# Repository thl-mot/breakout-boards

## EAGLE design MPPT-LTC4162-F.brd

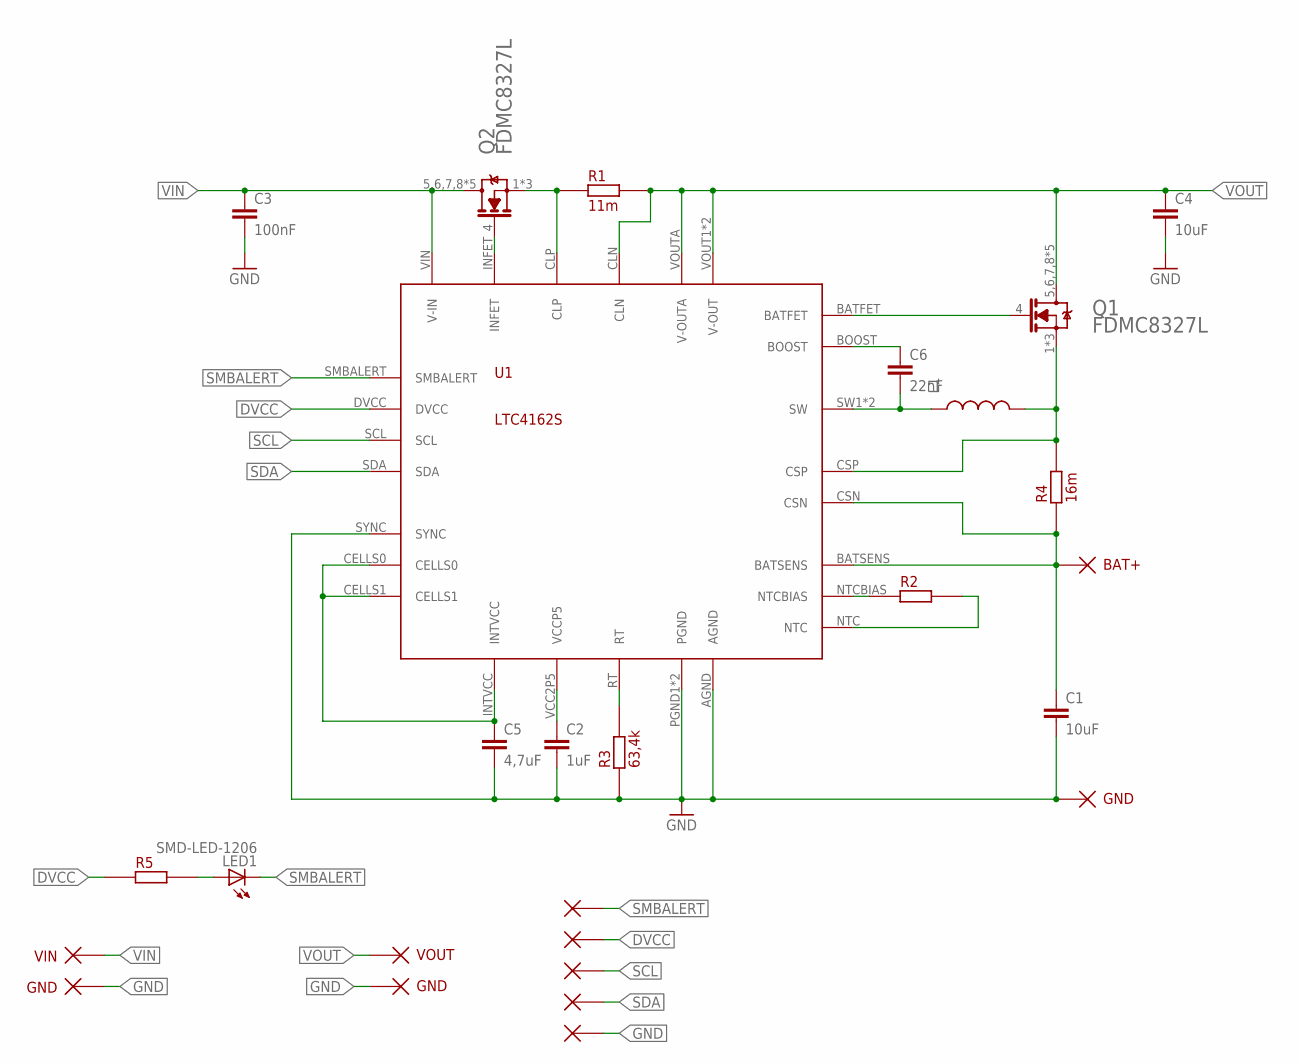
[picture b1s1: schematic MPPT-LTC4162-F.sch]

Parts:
C1, C4: 10uF; C1206
C2: 1uF; C1206
C3: 100nF; C1206
C5: 4,7uF; C1206
C6: 22nF; C1206
L1: L-242408FPS; L-SMD-FPD
LED1: SMD-LED-1206; LED_1206
P1: VIN; PIN
P2, P7, P10: GND; PIN
P3, P4, P5, P6, P11: PIN
P8: BAT+; PIN
P9: VOUT; PIN
Q1, Q2: N-MOSFET_FDMC8327LFDMC8327L; ON_SEMI_FDMC8327L_0
R1: 11m; C1206
R2: SMD-RR1206; C1206
R3: 63,4k; C1206
R4: 16m; C1206
R5: SMD-RR0603; R0603
U1: LTC4162S; QFN28-4X5MM

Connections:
DVCC: P4.P$1, R5.1, U1.DVCC
GND: C1.2, C2.2, C3.2, C4.2, C5.2, P2.P$1, P7.P$1, P10.P$1, P11.P$1, R3.1, U1.AGND, U1.PGND1 (PGND), U1.PGND2 (PGND), U1.SYNC
INFET: Q2.4 (G), U1.INFET
unnamed: C5.1, U1.CELLS0, U1.CELLS1, U1.INTVCC
unnamed: R3.2, U1.RT
unnamed: C2.1, U1.VCC2P5 (VCCP5)
unnamed: R2.1, U1.NTCBIAS
unnamed: R2.2, U1.NTC
unnamed: Q1.4 (G), U1.BATFET
unnamed: C1.1, P8.P$1, R4.1, U1.BATSENS, U1.CSN
unnamed: L1.2, Q1.1 (1_S), Q1.2 (1_S), Q1.3 (1_S), R4.2, U1.CSP
unnamed: C6.2, L1.1, U1.SW1 (SW), U1.SW2 (SW)
unnamed: C6.1, U1.BOOST
unnamed: Q2.1 (1_S), Q2.2 (1_S), Q2.3 (1_S), R1.1, U1.CLP
unnamed: LED1.A, R5.2
SCL: P5.P$1, U1.SCL
SDA: P6.P$1, U1.SDA
SMBALERT: LED1.C, P3.P$1, U1.SMBALERT
VIN: C3.1, P1.P$1, Q2.5,6,7,8 (D), Q2.5,6,7,8-2 (D), Q2.5,6,7,8-3 (D), Q2.5,6,7,8-4 (D), Q2.5,6,7,8-5 (D), U1.VIN (V-IN)
VOUT: C4.1, P9.P$1, Q1.5,6,7,8 (D), Q1.5,6,7,8-2 (D), Q1.5,6,7,8-3 (D), Q1.5,6,7,8-4 (D), Q1.5,6,7,8-5 (D), R1.2, U1.CLN, U1.VOUT1 (V-OUT), U1.VOUT2 (V-OUT), U1.VOUTA (V-OUTA)

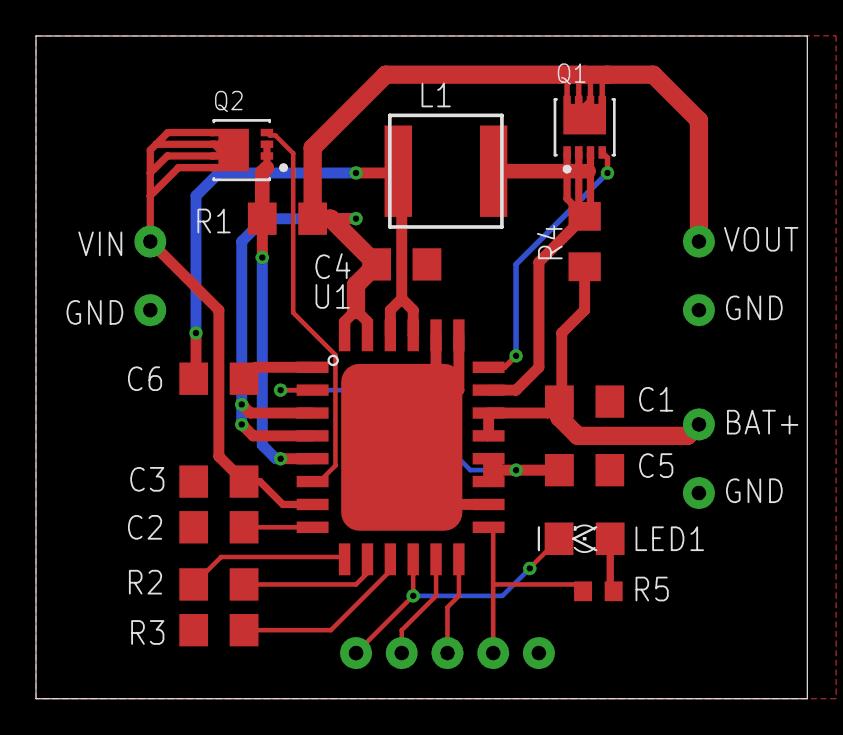
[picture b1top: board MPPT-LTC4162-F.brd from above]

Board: 2 copper layers, 42.9 x 36.8 mm, 27 parts (0 on the bottom side), 20 nets.

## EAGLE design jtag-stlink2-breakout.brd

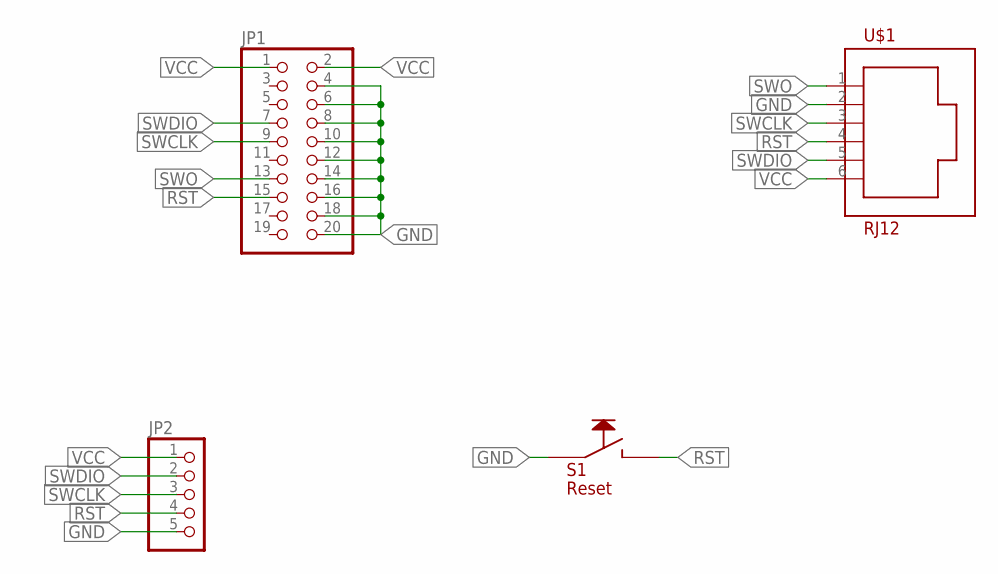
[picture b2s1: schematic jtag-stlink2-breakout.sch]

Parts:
JP1: PINHD-2X10; 2X10
JP2: PINHD-1X5; 1X05
S1: Reset; SMD-PUSH-BUTTON-ILS-3X6X2,5
U$1: RJ12

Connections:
GND: JP1.4, JP1.6, JP1.8, JP1.10, JP1.12, JP1.14, JP1.16, JP1.18, JP1.20, JP2.5, S1.P$1, U$1.2
RST: JP1.15, JP2.4, S1.P$2, U$1.4
SWCLK: JP1.9, JP2.3, U$1.3
SWDIO: JP1.7, JP2.2, U$1.5
SWO: JP1.13, U$1.1
VCC: JP1.1, JP1.2, JP2.1, U$1.6

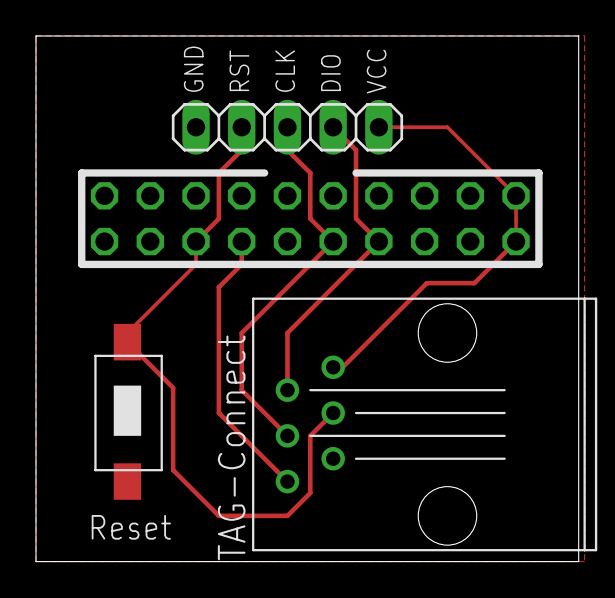
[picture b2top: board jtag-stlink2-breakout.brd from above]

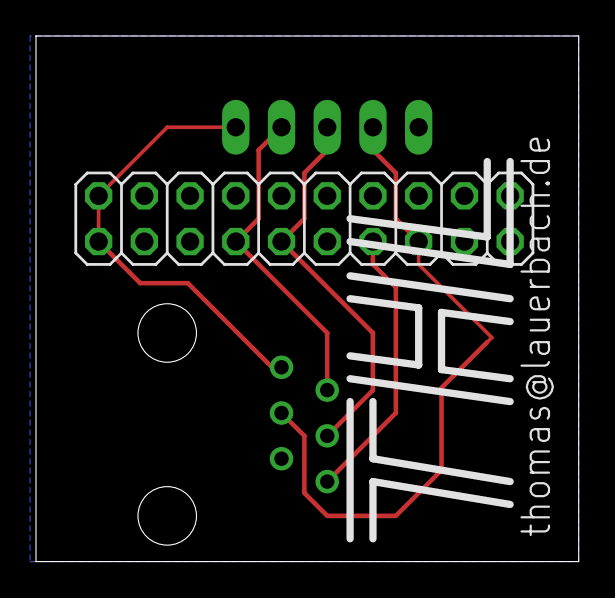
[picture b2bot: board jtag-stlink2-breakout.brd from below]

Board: 2 copper layers, 30.1 x 29.2 mm, 5 parts (2 on the bottom side), 6 nets.

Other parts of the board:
U$2: THL

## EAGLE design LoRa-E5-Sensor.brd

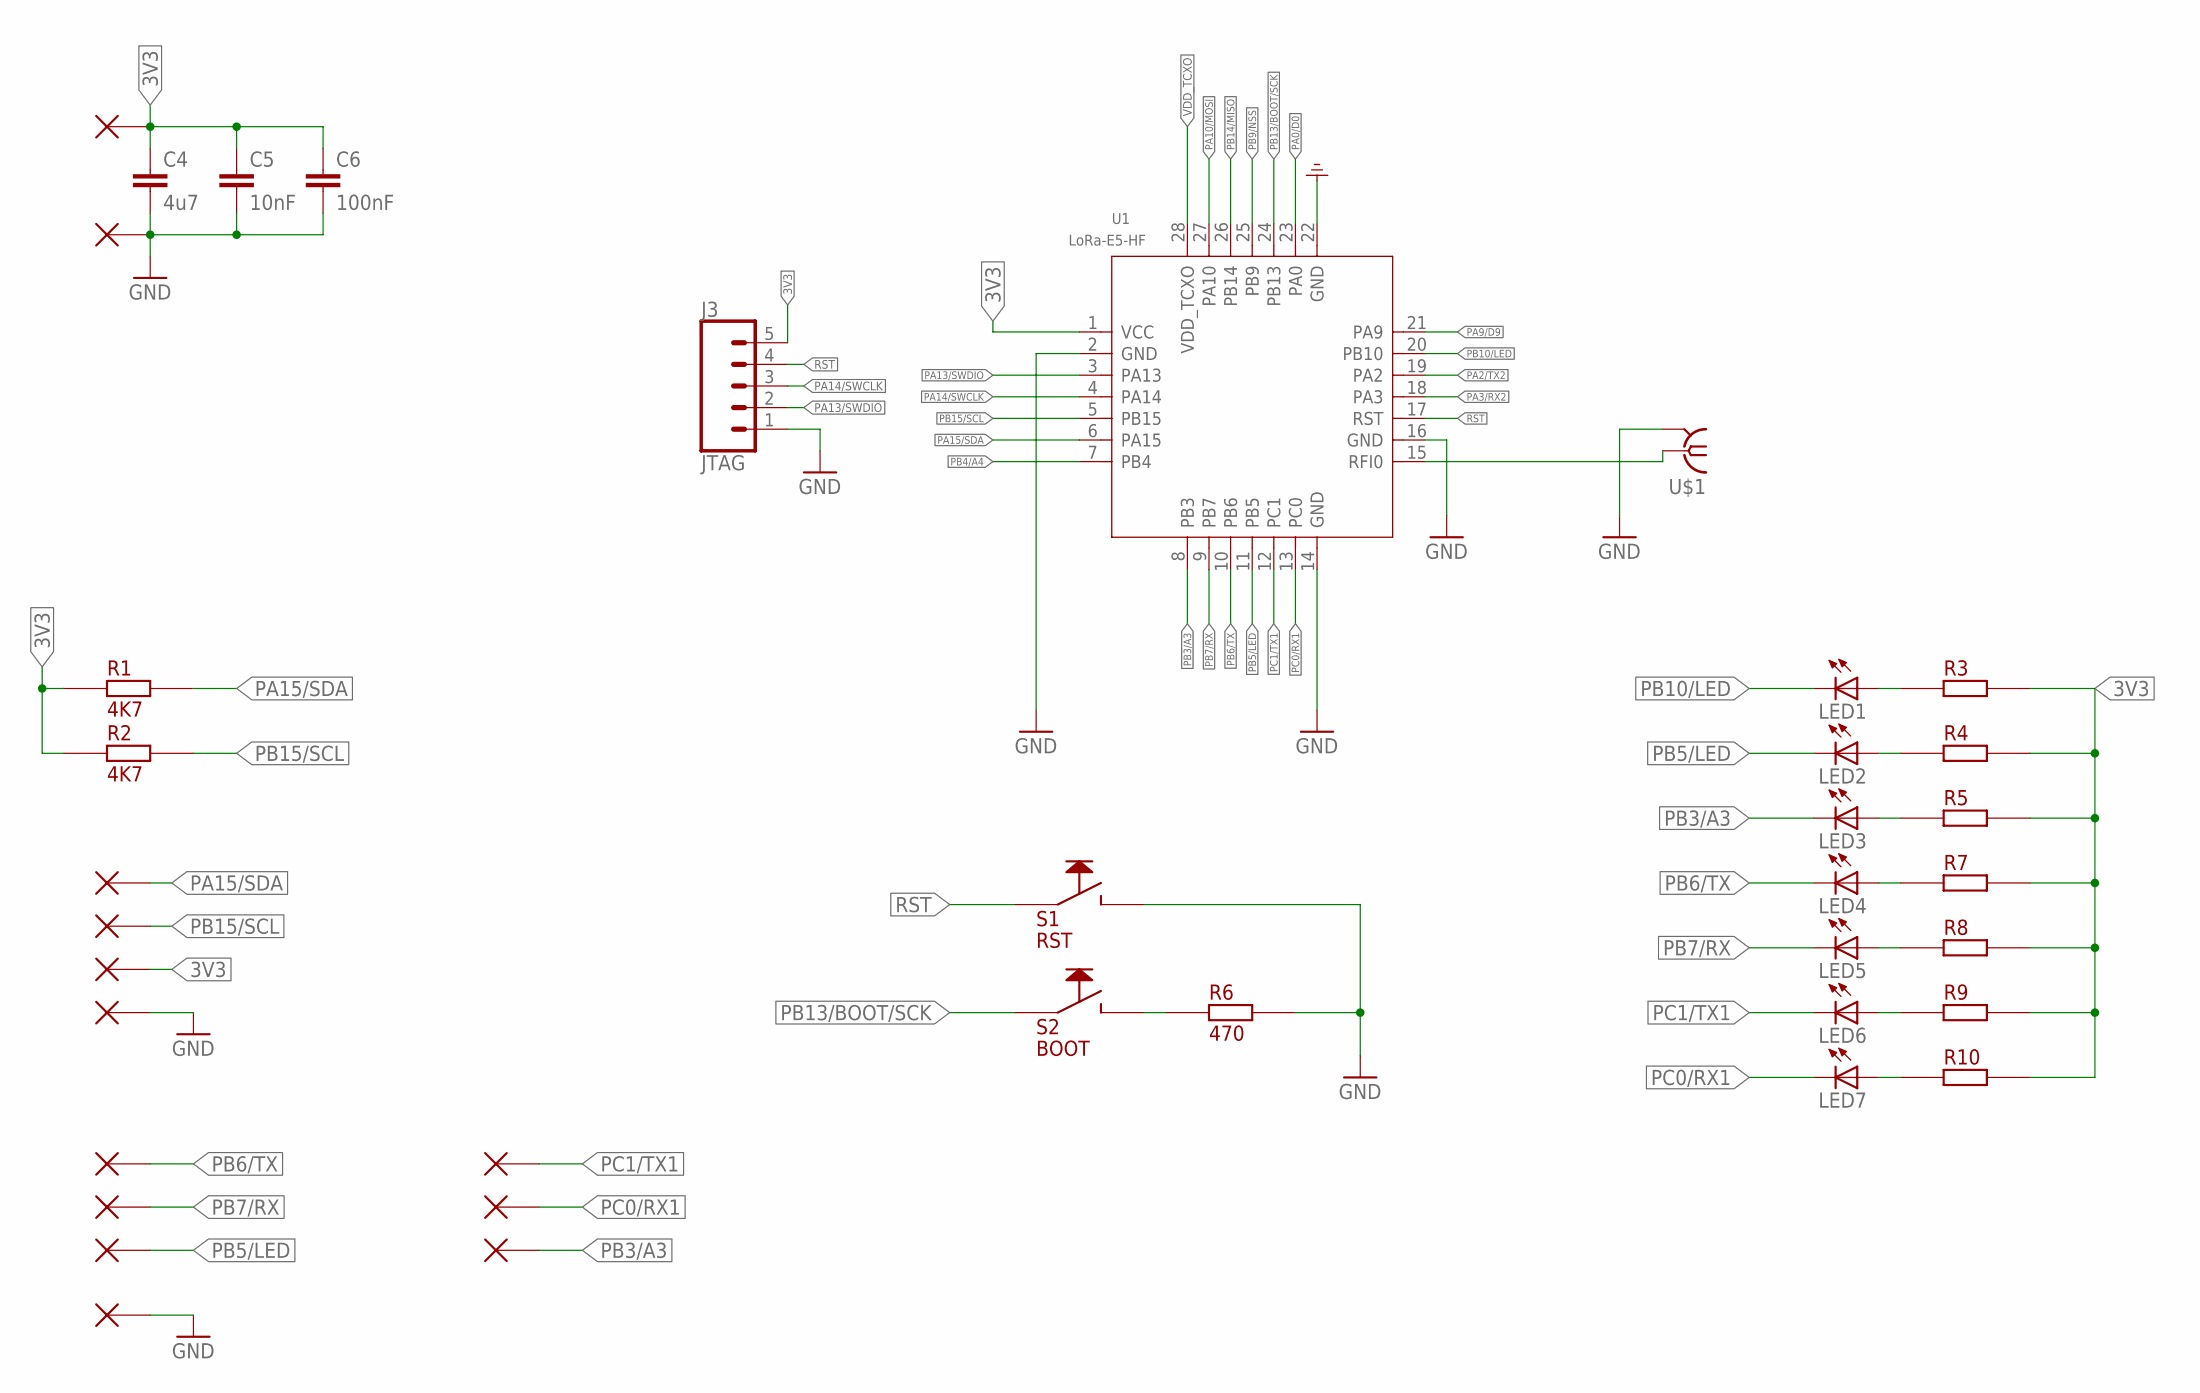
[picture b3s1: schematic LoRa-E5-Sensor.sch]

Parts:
C4: 4u7; C1206
C5: 10nF; C1206
C6: 100nF; C1206
J3: JTAG; 1X05_LOCK
LED1, LED2, LED3, LED4, LED5, LED6, LED7: SMD-LED-1206; LED_1206
P1, P2, P3, P4, P5, P6, P7, P8, P9, P10, P11, P12, P13: PIN
R1, R2: 4K7; R0603
R3, R4, R5, R7, R8, R9, R10: SMD-RR0603; R0603
R6: 470; C1206
S1: RST; SMD-PUSH-BUTTON-ILS-3X6X2,5
S2: BOOT; SMD-PUSH-BUTTON-ILS-3X6X2,5
U1: LoRa-E5-HF; MOUDLE28P-1.25-12X12X2.5MM
U$1: SMAU.FL; U.FL_SMT

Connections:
3V3: C4.1, C5.1, C6.1, J3.5, P4.P$1, P5.P$1, R1.1, R2.1, R3.2, R4.2, R5.2, R7.2, R8.2, R9.2, R10.2, U1.1 (VCC)
GND: C4.2, C5.2, C6.2, J3.1, P1.P$1, P6.P$1, P9.P$1, R6.2, S1.P$2, U1.2 (GND), U1.14 (GND), U1.16 (GND), U1.22 (GND), U$1.GND1 (SHIELD), U$1.GND2 (SHIELD)
unnamed: R6.1, S2.P$2
unnamed: U1.15 (RFI0), U$1.SIG (ANT)
unnamed: LED1.A, R3.1
unnamed: LED2.A, R4.1
unnamed: LED3.A, R5.1
unnamed: LED4.A, R7.1
unnamed: LED5.A, R8.1
unnamed: LED6.A, R9.1
unnamed: LED7.A, R10.1
PA0/D0: U1.23 (PA0)
PA2/TX2: U1.19 (PA2)
PA3/RX2: U1.18 (PA3)
PA9/D9: U1.21 (PA9)
PA10/MOSI: U1.27 (PA10)
PA13/SWDIO: J3.2, U1.3 (PA13)
PA14/SWCLK: J3.3, U1.4 (PA14)
PA15/SDA: P2.P$1, R1.2, U1.6 (PA15)
PB3/A3: LED3.C, P13.P$1, U1.8 (PB3)
PB4/A4: U1.7 (PB4)
PB5/LED: LED2.C, P12.P$1, U1.11 (PB5)
PB6/TX: LED4.C, P7.P$1, U1.10 (PB6)
PB7/RX: LED5.C, P8.P$1, U1.9 (PB7)
PB9/NSS: U1.25 (PB9)
PB10/LED: LED1.C, U1.20 (PB10)
PB13/BOOT/SCK: S2.P$1, U1.24 (PB13)
PB14/MISO: U1.26 (PB14)
PB15/SCL: P3.P$1, R2.2, U1.5 (PB15)
PC0/RX1: LED7.C, P11.P$1, U1.13 (PC0)
PC1/TX1: LED6.C, P10.P$1, U1.12 (PC1)
RST: J3.4, S1.P$1, U1.17 (RST)
VDD_TCXO: U1.28 (VDD_TCXO)

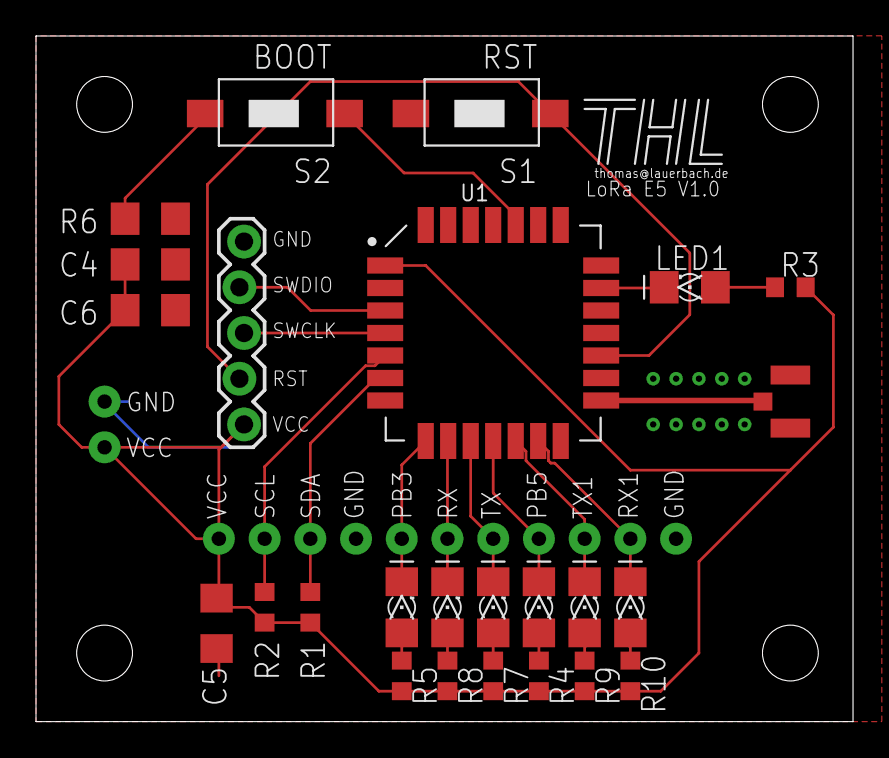
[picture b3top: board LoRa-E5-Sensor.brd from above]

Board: 2 copper layers, 45.4 x 38.1 mm, 43 parts (0 on the bottom side), 24 nets.

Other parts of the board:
U$2, U$3, U$4, U$5: BOHRUNG_3MM_UNTERLEGSCHEIBE
U$6: THL-SMALL

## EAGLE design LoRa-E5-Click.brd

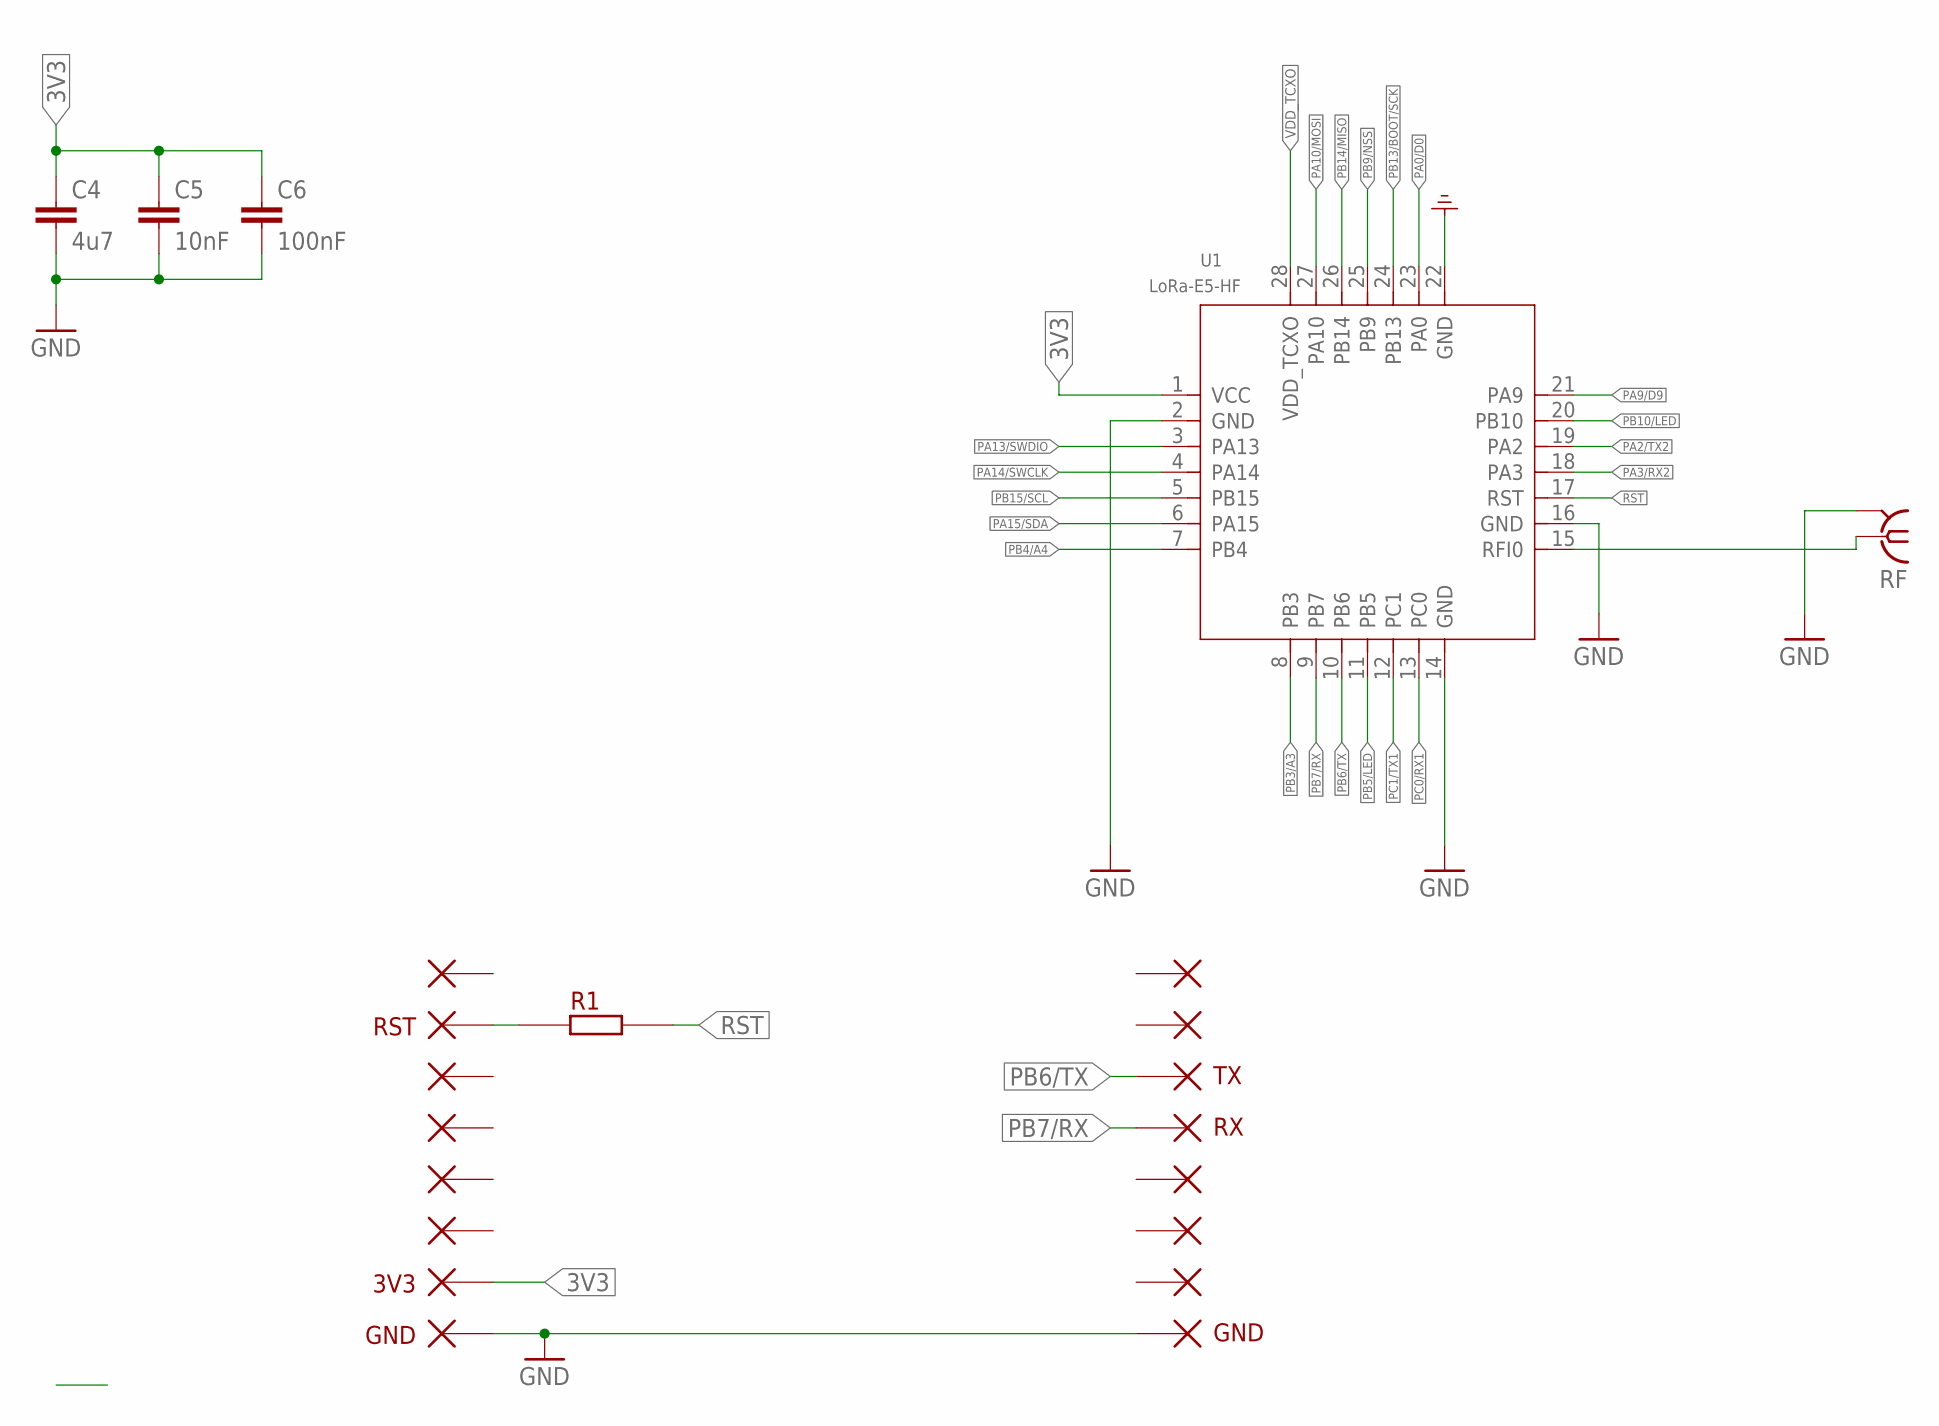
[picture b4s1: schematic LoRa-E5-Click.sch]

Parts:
C4: 4u7; C1206
C5: 10nF; C1206
C6: 100nF; C1206
P2, P7, P8, P9, P10, P13, P14, P17, P18, P19: PIN
P3: RST; PIN
P11: 3V3; PIN
P12, P20: GND; PIN
P15: TX; PIN
P16: RX; PIN
R1: SMD-RR0603; R0603
RF: SMAU.FL; U.FL_SMT
U1: LoRa-E5-HF; MOUDLE28P-1.25-12X12X2.5MM

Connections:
3V3: C4.1, C5.1, C6.1, P11.P$1, U1.1 (VCC)
GND: C4.2, C5.2, C6.2, P12.P$1, P20.P$1, RF.GND1 (SHIELD), RF.GND2 (SHIELD), U1.2 (GND), U1.14 (GND), U1.16 (GND), U1.22 (GND)
unnamed: RF.SIG (ANT), U1.15 (RFI0)
unnamed: P3.P$1, R1.1
PA0/D0: U1.23 (PA0)
PA2/TX2: U1.19 (PA2)
PA3/RX2: U1.18 (PA3)
PA9/D9: U1.21 (PA9)
PA10/MOSI: U1.27 (PA10)
PA13/SWDIO: U1.3 (PA13)
PA14/SWCLK: U1.4 (PA14)
PA15/SDA: U1.6 (PA15)
PB3/A3: U1.8 (PB3)
PB4/A4: U1.7 (PB4)
PB5/LED: U1.11 (PB5)
PB6/TX: P15.P$1, U1.10 (PB6)
PB7/RX: P16.P$1, U1.9 (PB7)
PB9/NSS: U1.25 (PB9)
PB10/LED: U1.20 (PB10)
PB13/BOOT/SCK: U1.24 (PB13)
PB14/MISO: U1.26 (PB14)
PB15/SCL: U1.5 (PB15)
PC0/RX1: U1.13 (PC0)
PC1/TX1: U1.12 (PC1)
RST: R1.2, U1.17 (RST)
VDD_TCXO: U1.28 (VDD_TCXO)

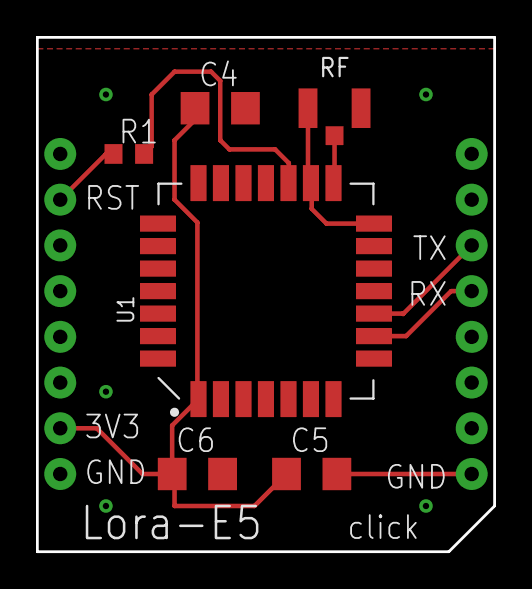
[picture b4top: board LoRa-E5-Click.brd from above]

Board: 2 copper layers, 25.4 x 28.6 mm, 23 parts (1 on the bottom side), 7 nets.

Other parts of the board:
U$2: THL

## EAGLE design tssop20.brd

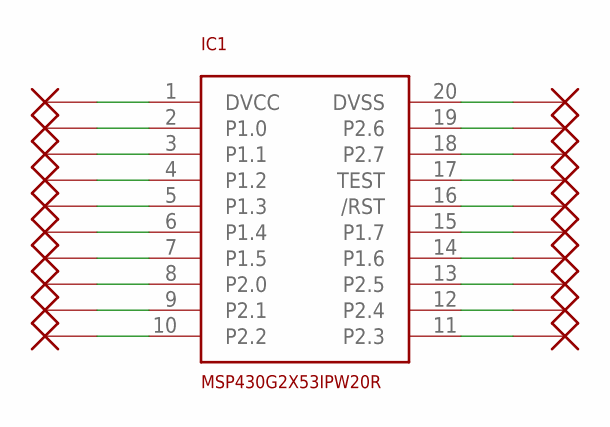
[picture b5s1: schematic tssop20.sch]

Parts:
IC1: MSP430G2X53IPW20R; TSSOP20
P1, P2, P3, P4, P5, P6, P7, P8, P9, P10, P15, P16, P17, P18, P19, P20, P21, P22, P23, P24: PIN

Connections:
unnamed: IC1.1 (DVCC), P1.P$1
unnamed: IC1.2 (P1.0), P2.P$1
unnamed: IC1.3 (P1.1), P3.P$1
unnamed: IC1.4 (P1.2), P4.P$1
unnamed: IC1.5 (P1.3), P5.P$1
unnamed: IC1.6 (P1.4), P6.P$1
unnamed: IC1.7 (P1.5), P7.P$1
unnamed: IC1.8 (P2.0), P8.P$1
unnamed: IC1.9 (P2.1), P9.P$1
unnamed: IC1.10 (P2.2), P10.P$1
unnamed: IC1.20 (DVSS), P15.P$1
unnamed: IC1.19 (P2.6), P16.P$1
unnamed: IC1.18 (P2.7), P17.P$1
unnamed: IC1.17 (TEST), P18.P$1
unnamed: IC1.16 (/RST), P19.P$1
unnamed: IC1.15 (P1.7), P20.P$1
unnamed: IC1.14 (P1.6), P21.P$1
unnamed: IC1.13 (P2.5), P22.P$1
unnamed: IC1.12 (P2.4), P23.P$1
unnamed: IC1.11 (P2.3), P24.P$1

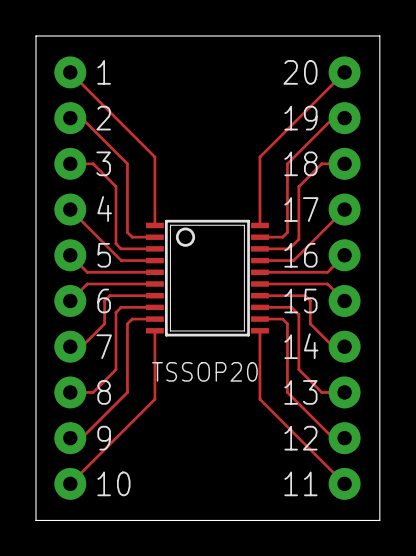
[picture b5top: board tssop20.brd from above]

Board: 2 copper layers, 19.1 x 26.9 mm, 22 parts (1 on the bottom side), 20 nets.

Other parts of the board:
U$1: THL

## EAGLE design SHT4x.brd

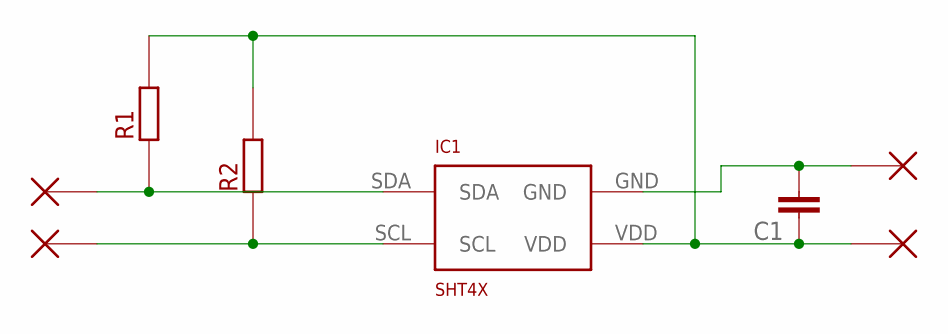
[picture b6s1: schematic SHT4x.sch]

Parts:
C1: SMD-C-1206; C1206
IC1: SHT4X
P1, P2, P3, P4: PIN
R1, R2: SMD-RR0603; R0603

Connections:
GND: C1.2, IC1.GND, P3.P$1
SCL: IC1.SCL, P2.P$1, R2.1
SDA: IC1.SDA, P1.P$1, R1.1
VDD: C1.1, IC1.VDD, P4.P$1, R1.2, R2.2

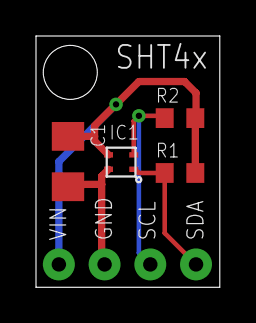
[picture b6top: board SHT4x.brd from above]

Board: 2 copper layers, 10.2 x 14.0 mm, 9 parts (1 on the bottom side), 4 nets.

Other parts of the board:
U$1: THL-SMALL

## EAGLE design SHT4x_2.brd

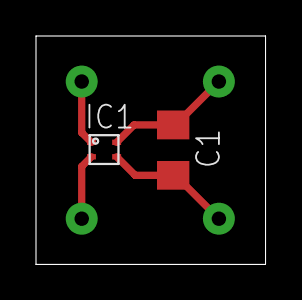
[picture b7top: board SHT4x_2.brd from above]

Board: 2 copper layers, 12.8 x 12.7 mm, 6 parts (0 on the bottom side), 4 nets.

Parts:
C1: C1206
IC1: SHT4X
P1, P2, P3, P4: PIN

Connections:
GND: C1.2, IC1.VDD, P3.P$1
unnamed: C1.1, IC1.VSS, P4.P$1
unnamed: IC1.SCL, P2.P$1
SDA: IC1.SDA, P1.P$1

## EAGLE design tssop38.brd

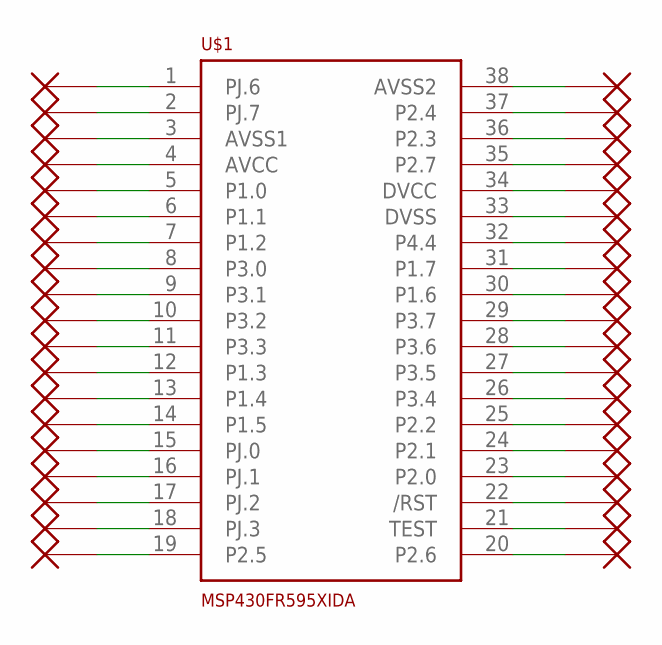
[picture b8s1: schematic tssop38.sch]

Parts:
P1, P2, P3, P4, P5, P6, P7, P8, P9, P10, P11, P12, P13, P14, P15, P16, P17, P18, P19, P20, P21, P22, P23, P24, P25, P26, P27, P28, P29, P30, P31, P32, P33, P34, P35, P36, P37, P38: PIN
U$1: MSP430FR595XIDA; TSSOP38

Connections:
unnamed: P1.P$1, U$1.1 (PJ.6)
unnamed: P2.P$1, U$1.2 (PJ.7)
unnamed: P3.P$1, U$1.3 (AVSS1)
unnamed: P4.P$1, U$1.4 (AVCC)
unnamed: P5.P$1, U$1.5 (P1.0)
unnamed: P6.P$1, U$1.6 (P1.1)
unnamed: P7.P$1, U$1.7 (P1.2)
unnamed: P8.P$1, U$1.8 (P3.0)
unnamed: P9.P$1, U$1.9 (P3.1)
unnamed: P10.P$1, U$1.10 (P3.2)
unnamed: P11.P$1, U$1.11 (P3.3)
unnamed: P12.P$1, U$1.12 (P1.3)
unnamed: P13.P$1, U$1.13 (P1.4)
unnamed: P14.P$1, U$1.14 (P1.5)
unnamed: P15.P$1, U$1.15 (PJ.0)
unnamed: P16.P$1, U$1.16 (PJ.1)
unnamed: P17.P$1, U$1.17 (PJ.2)
unnamed: P18.P$1, U$1.18 (PJ.3)
unnamed: P19.P$1, U$1.19 (P2.5)
unnamed: P20.P$1, U$1.20 (P2.6)
unnamed: P21.P$1, U$1.21 (TEST)
unnamed: P22.P$1, U$1.22 (/RST)
unnamed: P23.P$1, U$1.23 (P2.0)
unnamed: P24.P$1, U$1.24 (P2.1)
unnamed: P25.P$1, U$1.25 (P2.2)
unnamed: P26.P$1, U$1.26 (P3.4)
unnamed: P27.P$1, U$1.27 (P3.5)
unnamed: P28.P$1, U$1.28 (P3.6)
unnamed: P29.P$1, U$1.29 (P3.7)
unnamed: P30.P$1, U$1.30 (P1.6)
unnamed: P31.P$1, U$1.31 (P1.7)
unnamed: P32.P$1, U$1.32 (P4.4)
unnamed: P33.P$1, U$1.33 (DVSS)
unnamed: P34.P$1, U$1.34 (DVCC)
unnamed: P35.P$1, U$1.35 (P2.7)
unnamed: P36.P$1, U$1.36 (P2.3)
unnamed: P37.P$1, U$1.37 (P2.4)
unnamed: P38.P$1, U$1.38 (AVSS2)

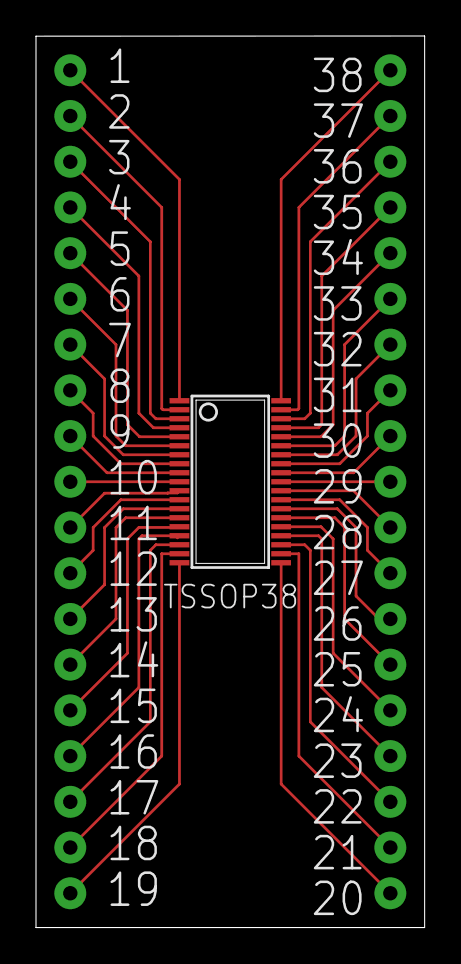
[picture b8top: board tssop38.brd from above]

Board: 2 copper layers, 21.6 x 49.5 mm, 40 parts (1 on the bottom side), 38 nets.

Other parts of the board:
U$2: THL

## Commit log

2021-09-22 things
2021-10-23 LoRa-E5
2021-12-08 new boards

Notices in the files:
parts and their libraries:
SparkFun-Aesthetics: Licensing: Creative Commons ShareAlike 4.0 International - https://creativecommons.org/licenses/by-sa/4.0
